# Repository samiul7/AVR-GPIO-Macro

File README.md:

# AVR-GPIO-Macro
A little easier to read and write of the GPIO register for AVR microcontroller.

## Macros list:

Set bit, Clear bit
* SBI(TCCR1A,WGM10) //WGM10 bit HIGH "set bit"
* CIB(TCCR1A,WGM10) //WGM10 bit LOW  "clear bit"

Individual pin mode settings
* SET_OUTPUT(PB7); 
* SET_INPUT(PB7);
* PULLUP(PB7);

Pin mode settings as a function
* PIN_MODE(PB7,OUTPUT);
* PIN_MODE(PB7,INPUT);
* PIN_MODE(PB7,INPUT_PULLUP);

Read and write of a GPIO
* WRITE(PB7, HIGH); 
* WRITE(PB7, LOW);
* READ(PB7);
* TOGGLE(PB7);

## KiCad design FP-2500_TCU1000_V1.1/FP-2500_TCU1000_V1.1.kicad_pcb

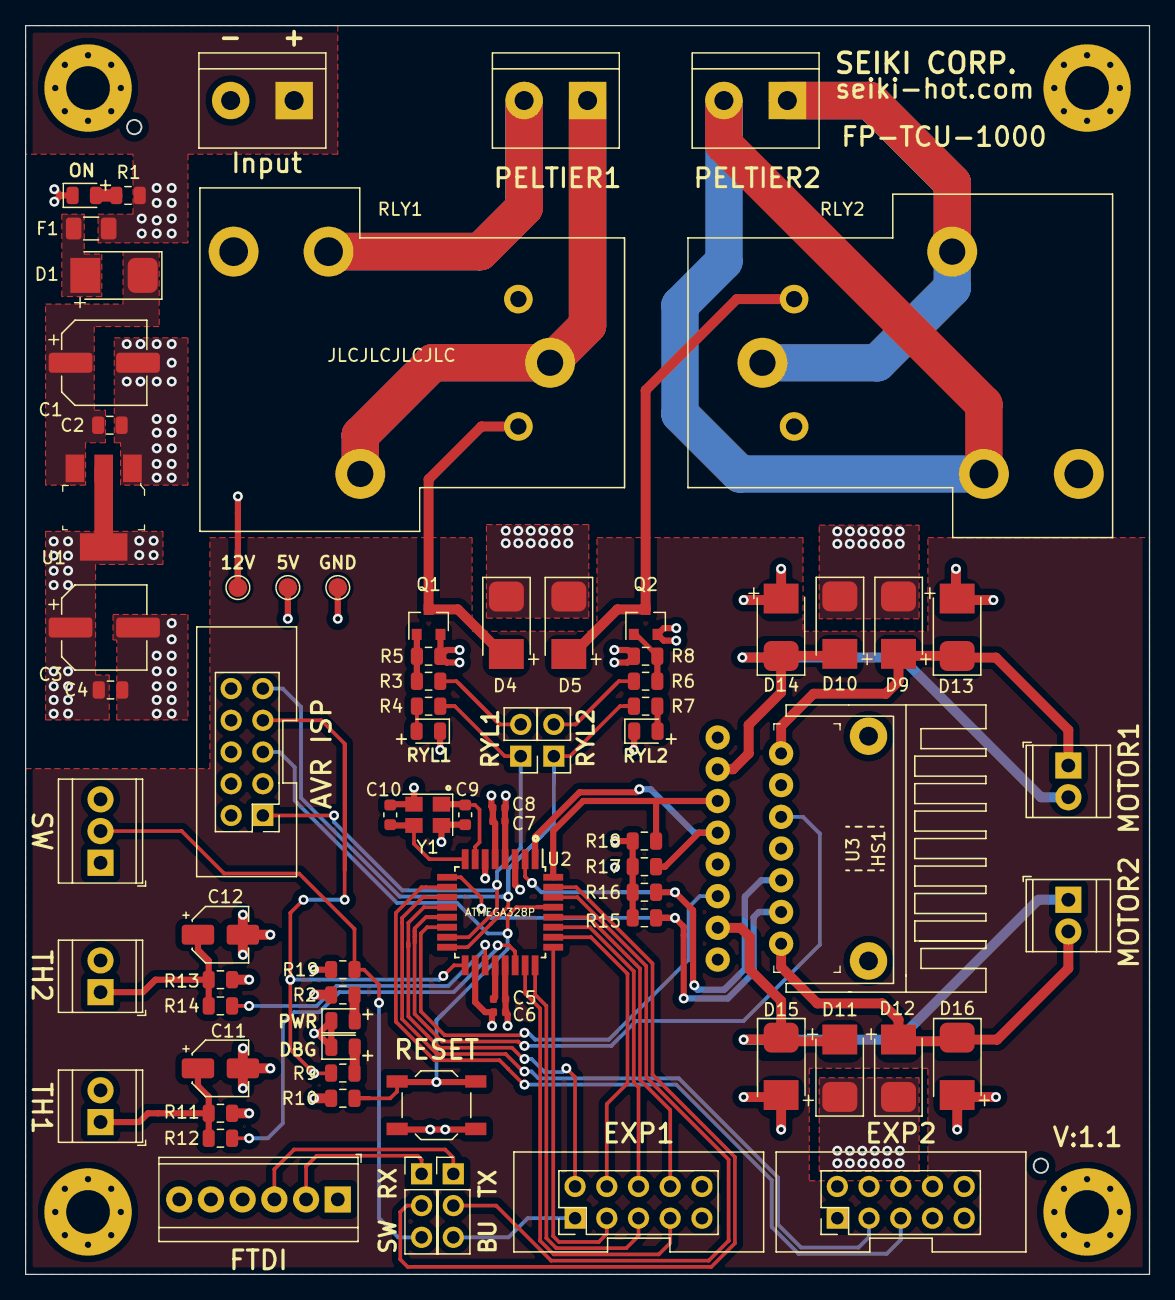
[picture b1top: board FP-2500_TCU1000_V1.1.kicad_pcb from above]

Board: 4 copper layers, 90.0 x 100.0 mm, 81 parts (0 on the bottom side), 56 nets.

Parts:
C1, C3: 47uF 35V; CP_Elec_6.3x7.7
C2, C4: 100nF; C_0805_2012Metric
C5, C6, C7, C8: 100nF; C_0402_1005Metric
C9, C10: 22pF; C_0603_1608Metric
C11, C12: 10uF 35V; CP_Elec_4x5.3
D1, D4, D5, D9, D10, D11, D12, D13, D14, D15, D16: M7; DO-214AC
D2, D3, D6, D7: LED; LED_0805_2012Metric
D8: DBG_LED; LED_0805_2012Metric
F1: SF-1206F200; Fuse_1206_3216Metric
H1, H2, H3, H4: MountingHole; MountingHole_3.5mm_Pad_Via
HS1: Heatsink; Heatsin25x23x16mm_2x_1.5mm
J1: EXP1; PinHeader_2x05_P2.54mm_Vertical
J2: EXP2; PinHeader_2x05_P2.54mm_Vertical
J3: Power Input; TerminalBlock_bornier-2_P5.08mm
J4: Peltier Out1; TerminalBlock_bornier-2_P5.08mm
J5: Peltier Out2; TerminalBlock_bornier-2_P5.08mm
J6: AVR ISP; PinHeader_2x05_P2.54mm_Vertical
J7: Thermitor 1; TerminalBlock_TE_282834-2_1x02_P2.54mm_Horizontal
J8: Thermitor 2; TerminalBlock_TE_282834-2_1x02_P2.54mm_Horizontal
J9: Motor Out1; TerminalBlock_TE_282834-2_1x02_P2.54mm_Horizontal
J10: Motor Out2; TerminalBlock_TE_282834-2_1x02_P2.54mm_Horizontal
J11: FTDI; TerminalBlock_TE_282834-6_1x06_P2.54mm_Horizontal
J12: KILL_SW; TerminalBlock_TE_282834-3_1x03_P2.54mm_Horizontal
JP1, JP2: JUMPER; PinHeader_1x02_P2.54mm_Vertical
JP3: TX_BUZZER; PinHeader_1x03_P2.54mm_Vertical
JP4: RX_KILL; PinHeader_1x03_P2.54mm_Vertical
Q1, Q2: MMBT3904; SOT-23
R1: 2.2K; R_0805_2012Metric
R2, R3, R4, R6, R7, R9: 1K; R_0805_2012Metric
R5, R8, R10, R15, R16, R17, R18, R19: 10K; R_0805_2012Metric
R11, R13: 4.7K; R_0805_2012Metric
R12, R14: 100; R_0805_2012Metric
RLY1, RLY2: 832-1A-C-12VDC
S1: RESET; SW_SPST_TL3342
TP1: +5V; TestPoint_Pad_D1.5mm
TP2: +12V; TestPoint_Pad_D1.5mm
TP3: GND; TestPoint_Pad_D1.5mm
U1: NCP1117ST50T3G; SOT-223
U2: ATMEGA328-AU; TQFP-32_7x7mm_P0.8mm
U3: L298N; Multiwatt-15
Y1: 16MHz; Crystal_SMD_3225-4Pin_3.2x2.5mm

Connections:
/AREF: C5.1, U2.20
/BTN_EN1: J2.3, U2.11
/BTN_EN2: J2.5, U2.10
/BTN_ENC: J1.2, U2.12
/BUZZER: J1.1, JP3.3
/KILL_SW: J12.2, JP4.3, R19.2
/LCD_D4: J1.5, U2.24
/LCD_D5: J1.6, U2.27
/LCD_D6: J1.7, U2.23
/LCD_D7: J1.8, U2.28
/LCD_EN: J1.3, U2.25
/LCD_RS: J1.4, U2.26
/M1_EN: U2.13, U3.6
/M1_IN1: R18.2, U2.32, U3.5
/M1_IN2: R17.2, U2.1, U3.7
/M2_EN: U2.14, U3.11
/M2_IN1: R16.2, U2.2, U3.10
/M2_IN2: R15.2, U2.9, U3.12
/MISO_PL2: J6.9, JP2.1, R7.1, U2.16
/MOSI_PL1: J6.1, JP1.1, R4.1, U2.15
/RST: J6.5, R10.2, S1.1, U2.29
/RX: J11.2, JP4.1
/RX_KILL: JP4.2, U2.31
/SCK: J6.7, R9.1, U2.17
/TH1: R12.2, U2.22
/TH2: R14.2, U2.19
/TX: J11.3, JP3.1
/TX_BUZ: JP3.2, U2.30
/XTAL1: C9.1, U2.7, Y1.1
/XTAL2: C10.1, U2.8, Y1.3
GND: C1.2, C2.2, C3.2, C4.2, C5.2, C6.2, C7.2, C8.2, C9.2, C10.2, C11.2, C12.2, D2.1, D3.1, D6.1, D7.1, D8.1, D13.2, D14.2, D15.2, D16.2, J1.9, J2.9, J3.2, J6.4, J6.6, J6.8, J6.10, J7.2, J8.2, J11.6, J12.3, Q1.2, Q2.2, R5.2, R8.2, S1.2, TP3.1, U1.1, U2.3, U2.5, U2.21, U3.1, U3.8, U3.15, Y1.2, Y1.4
unnamed: C1.1, C2.1, D1.1, U1.3
unnamed: C11.1, J7.1, R11.2, R12.1
unnamed: C12.1, J8.1, R13.2, R14.1
unnamed: D1.2, F1.1
unnamed: D2.2, R1.2
unnamed: D3.2, R2.2
unnamed: D4.2, Q1.3, RLY1.2
unnamed: D5.2, Q2.3, RLY2.2
unnamed: D6.2, R4.2
unnamed: D7.2, R7.2
unnamed: D8.2, R9.2
unnamed: D10.2, D14.1, J9.2, U3.3
unnamed: D11.2, D15.1, J10.1, U3.13
unnamed: D12.2, D16.1, J10.2, U3.14
unnamed: D9.2, D13.1, J9.1, U3.2
unnamed: J4.1, RLY1.4
unnamed: J4.2, RLY1.5
unnamed: J5.1, RLY2.4
unnamed: J5.2, RLY2.5
unnamed: JP1.2, R3.2
unnamed: JP2.2, R6.2
unnamed: Q1.1, R3.1, R5.1
unnamed: Q2.1, R6.1, R8.1
VBUS: D4.1, D5.1, D9.1, D10.1, D11.1, D12.1, F1.2, J3.1, R1.1, RLY1.1, RLY2.1, TP2.1, U3.4
VCC: C3.1, C4.1, C6.1, C7.1, C8.1, J1.10, J6.2, J11.4, J12.1, R2.1, R10.1, R11.1, R13.1, R15.1, R16.1, R17.1, R18.1, R19.1, TP1.1, U1.2, U1.4, U2.4, U2.6, U2.18, U3.9

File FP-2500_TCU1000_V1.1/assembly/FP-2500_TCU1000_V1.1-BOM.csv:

Comment,Designator,Footprint,LCSC
47uF 35V,"C1,C3",Capacitor_SMD:CP_Elec_6.3x7.7,C131122
100nF,"C2,C4",Capacitor_SMD:C_0805_2012Metric,C49678
100nF,"C5,C6,C7,C8",Capacitor_SMD:C_0402_1005Metric,C307331
22pF,"C9,C10",Capacitor_SMD:C_0603_1608Metric,C1653
10uF 35V,"C11,C12",Capacitor_SMD:CP_Elec_4x5.3,C72485
M7,"D1,D4,D5,D9,D10,D11,D12,D13,D14,D15,D16",Diode:DO-214AC,C95872
LED,D2,LED_SMD:LED_0805_2012Metric,C34499
LED,D3,LED_SMD:LED_0805_2012Metric,C2297
LED,"D6,D7",LED_SMD:LED_0805_2012Metric,C2296
DBG_LED,D8,LED_SMD:LED_0805_2012Metric,C2296
SF-1206F200,F1,Fuse:Fuse_1206_3216Metric,C719183
MMBT3904,"Q1,Q2",Package_TO_SOT_SMD:SOT-23,C20526
2.2K,R1,Resistor_SMD:R_0805_2012Metric,C17520
1K,"R2,R3,R4,R6,R7,R9",Resistor_SMD:R_0805_2012Metric,C17379
10K,"R5,R8,R10,R15,R16,R17,R18,R19",Resistor_SMD:R_0805_2012Metric,C17414
4k7,"R11,R13",Resistor_SMD:R_0805_2012Metric,C17673
100,"R12,R14",Resistor_SMD:R_0805_2012Metric,C17408
RESET,S1,Button_Switch_SMD:SW_SPST_TL3342,C318888
NCP1117ST50T3G,U1,digikey-footprints:SOT-223,C17314
16MHz,Y1,Crystal:Crystal_SMD_3225-4Pin_3.2x2.5mm,C13738

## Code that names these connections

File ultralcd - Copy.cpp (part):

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
void rotaryEncoder_Init()
{
  pinMode(BUZZER_IO, OUTPUT);
  pinMode(BTN_EN1, INPUT_PULLUP);
  pinMode(BTN_EN2, INPUT_PULLUP);
  pinMode(BTN_ENC, INPUT_PULLUP);

  rotary_buttons_update();
  encoderpos = 0;
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
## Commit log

2021-11-04 Rename ultralcd - Copy.cpp to ultralcd.cpp
2021-11-05 Rename ultralcd.cpp to ultralcd_old.cpp
